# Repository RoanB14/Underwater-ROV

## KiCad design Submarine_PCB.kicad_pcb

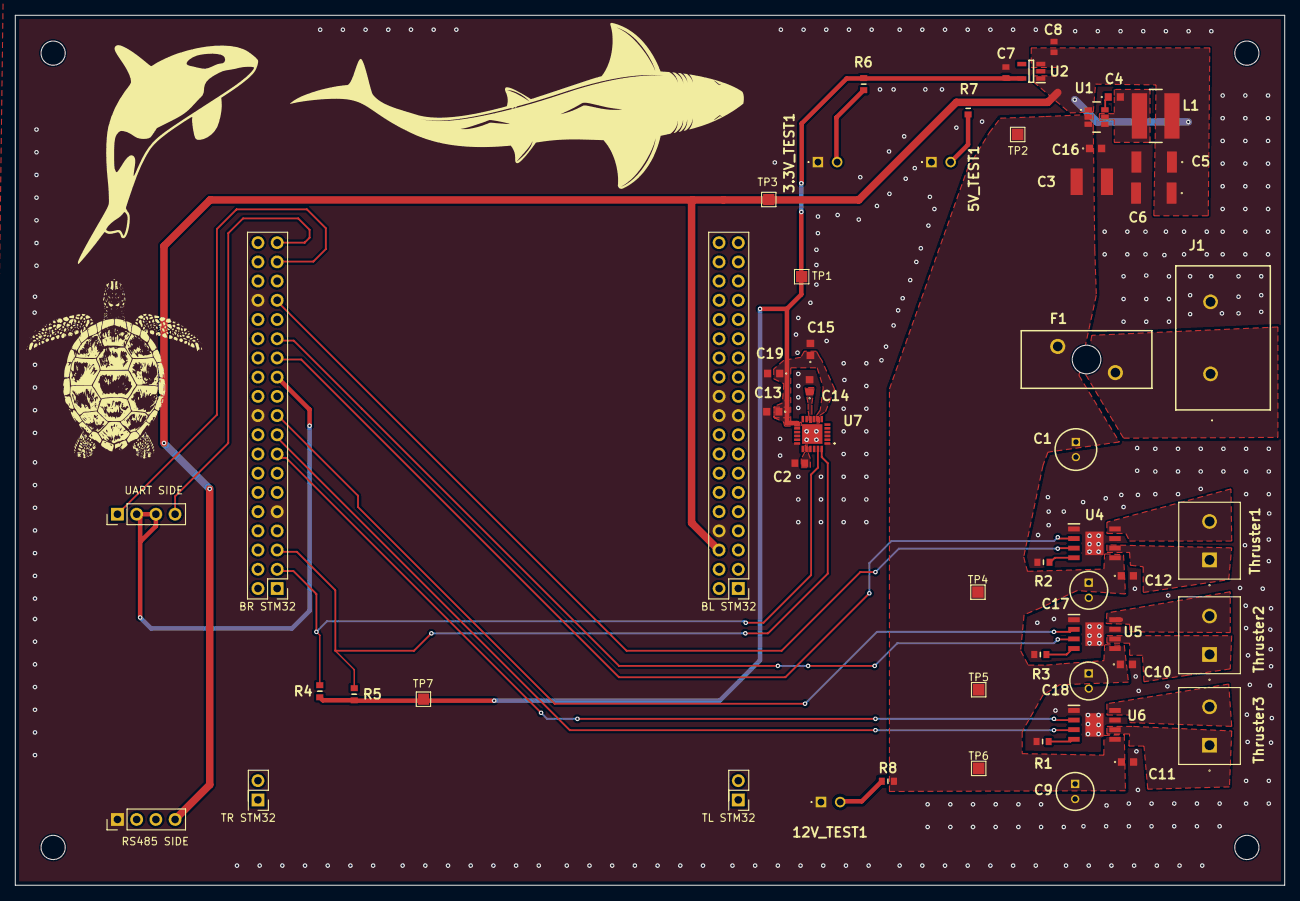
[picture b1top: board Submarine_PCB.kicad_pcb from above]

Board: 2 copper layers, 167.8 x 115.0 mm, 55 parts (0 on the bottom side), 23 nets.

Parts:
3.3V_TEST1, 5V_TEST1, 12V_TEST1: LED; WP710A10ID
BL STM32: PinHeader_2x19_P2.54mm_Vertical
BR STM32: PinHeader_2x19_P2.54mm_Vertical
C1: 100uF 25V; CAPPRD200W50D550H1250
C2: 2.2nF; CAPC1608X95N
C3: 10μF; C1812_FT
C4, C16: 100nF; C0603
C5, C6: 22μF; C4532_Commercial
C7, C8: 1μF; CAPC1608X90N
C9, C17, C18: 47μF; CAPPRD200W50D500H1250
C10, C11, C12, C13, C14: 0.1μF; C0603
C15: 10nF; C0603
C19: 1μF; C0603
F1: Fuse; 01530008
J1: Screw_Terminal_01x02; 1714971
L1: 4.7μH; SRN6045_1
R1, R2, R3: 18kΩ; RESC1608X55N
R4, R5: 4.7kΩ; RESC1608X55N
R6: 270Ω; RESC1608X55N
R7: 620Ω; RESC1608X55N
R8: 2kΩ; RESC1608X55N
RS485 SIDE: PinHeader_1x04_P2.54mm_Vertical
TL STM32: PinHeader_1x02_P2.54mm_Vertical; PinHeader_2x02_P2.54mm_Vertical
TP1, TP2, TP3, TP4, TP5, TP6, TP7: TestPoint; TestPoint_Pad_1.5x1.5mm
TR STM32: PinHeader_1x02_P2.54mm_Vertical; PinHeader_2x02_P2.54mm_Vertical
Thruster1, Thruster2, Thruster3: Motor_DC; 1729128
U1: AP63205WU; AP63205WU7
U2: MIC5504-3.3YM5; SOT95P280X145-5N
U4, U5, U6: DRV8871DDA; SOIC127P600X170-9N
U7: MPU-6050; MPU6050
UART SIDE: PinHeader_1x04_P2.54mm_Vertical

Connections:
3.3V: C7.1, C13.1, C15.1, C19.1, R4.2, R5.2, R6.1, TP1.1, TP7.1, U2.5 (VOUT), U7.8 (VLOGIC), U7.13 (VDD)
5V: C5.1, C6.1, C8.1, L1.1, R7.2, RS485 SIDE.4, TP3.1, U1.1 (FB), U2.1 (VIN), U2.3 (EN)
12V_Fused: C1.1, C3.1, C9.1, C10.1, C11.1, C12.1, C16.1, C17.1, C18.1, F1.1, R8.1, TP2.1, TP4.1, TP5.1, TP6.1, U1.2 (EN), U1.3 (IN), U4.5 (VM), U5.5 (VM), U6.5 (VM)
/12V: F1.2, J1.1
GND: 3.3V_TEST1.1 (K), 5V_TEST1.1 (K), 12V_TEST1.1 (K), BL STM32.8, BL STM32.19, BL STM32.20, BL STM32.22, BR STM32.9, BR STM32.20, BR STM32.32, C1.2, C2.2, C3.2, C5.2, C6.2, C7.2, C8.2, C9.2, C10.2, C11.2, C12.2, C13.2, C14.2, C15.2, C16.2, C17.2, C18.2, C19.2, J1.2, R1.2, R2.2, R3.2, RS485 SIDE.1, U1.4 (GND), U2.2 (GND), U4.1 (GND), U4.7 (GND), U4.9 (GND), U5.1 (GND), U5.7 (GND), U5.9 (GND), U6.1 (GND), U6.7 (GND), U6.9 (GND), U7.1 (CLKIN), U7.9 (AD0), U7.11 (FSYNC), U7.18 (GND)
unnamed: 3.3V_TEST1.2 (A), R6.2
unnamed: 5V_TEST1.2 (A), R7.1
unnamed: 12V_TEST1.2 (A), R8.2
unnamed: Thruster1.1 (+), U4.6 (OUT1)
unnamed: Thruster1.2 (-), U4.8 (OUT2)
unnamed: Thruster2.1 (+), U5.6 (OUT1)
unnamed: Thruster2.2 (-), U5.8 (OUT2)
unnamed: Thruster3.1 (+), U6.6 (OUT1)
unnamed: Thruster3.2 (-), U6.8 (OUT2)
unnamed: C4.1, U1.6 (BST)
unnamed: C4.2, L1.2, U1.5 (SW)
unnamed: R2.1, U4.4 (ILIM)
unnamed: R3.1, U5.4 (ILIM)
unnamed: R1.1, U6.4 (ILIM)
unnamed: C2.1, U7.20 (CPOUT)
unnamed: C14.1, U7.10 (REGOUT)
SCL: R4.1, U7.23 (SCL)
SDA: R5.1, U7.24 (SDA)

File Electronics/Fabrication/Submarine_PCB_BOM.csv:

Designator,Comment,Footprint,JLCPCB Part #
"3.3V_TEST1,5V_TEST1,12V_TEST1",LED,SamacSys_Parts:WP710A10ID,C5831626
C1,100uF 25V,SamacSys_Parts:CAPPRD200W50D550H1250,C108360
C2,2.2nF,SamacSys_Parts:CAPC1608X95N,C2199229
C3,10uF,SamacSys_Parts:C1812_FT,C3904240
"C4,C16",100nF,SamacSys_Parts:C0603,C127833
"C5,C6",22uF,SamacSys_Parts:C4532_Commercial,C1845355
"C7,C8",1uF,SamacSys_Parts:CAPC1608X90N,C29936
"C9,C17,C18",47uF,SamacSys_Parts:CAPPRD200W50D500H1250,C1580484
"C10,C11,C12,C13,C14",0.1uF,SamacSys_Parts:C0603,C127833
C15,10nF,SamacSys_Parts:C0603,C19271112
C19,1uF,SamacSys_Parts:C0603,C29936
F1,Fuse,SamacSys_Parts:01530008,C206907
J1,Screw_Terminal_01x02,SamacSys_Parts:1714971,C92145
L1,4.7uH,SamacSys_Parts:SRN6045_1,C780210
"R1,R2,R3",18k,SamacSys_Parts:RESC1608X55N,C137655
"R4,R5",4.7k,SamacSys_Parts:RESC1608X55N,C99782
R6,270,SamacSys_Parts:RESC1608X55N,C137754
R7,620,SamacSys_Parts:RESC1608X55N,C137695
R8,2k,SamacSys_Parts:RESC1608X55N,C105576
"Thruster1,Thruster2,Thruster3",Motor_DC,SamacSys_Parts:1729128,C7509570
U1,AP63205WU,SamacSys_Parts:AP63205WU7,C2071056
U2,MIC5504-3.3YM5,SamacSys_Parts:SOT95P280X145-5N,C88419
"U4,U5,U6",DRV8871DDA,SamacSys_Parts:SOIC127P600X170-9N,C75864
U7,MPU-6050,SamacSys_Parts:MPU6050,C24112

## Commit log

2026-05-25 First commit with all kicad files
2026-05-29 Reorganized Kicad files and imported STM32 project
2026-05-29 Add global gitignore
2026-05-29 Restructured repo
